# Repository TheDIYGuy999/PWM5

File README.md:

# This is an Arduino "PWM5" Solar Charge Controller

It was originally invented by Julian Ilett: https://www.youtube.com/watch?v=AobcNhLG_Xw&list=PLjzGSu1yGFjWa5BEHgX5UUrSexppett3W

This Arduino version uses a similar layout as arduined.eu: https://www.arduined.eu/arduino-solar-charge-controller/

After I designed and built a couple of own MPPT solar chargers (see my other Repositories here), I wanted to try this "classic" PWM design.
It works fine, but of course you can't use it for nominal voltages below 12V (or at least it would be very inefficient in this case). Check out the included PCB files, if you want to build your own PWM5 controller.

## Features / Improvements:
- Programmable with Arduino IDE
- Input voltage 12 - 22V (36 cell solar panel)
- Output voltage 10.8 - 14.4V (6 cell 12V lead acid battery)
- Suitable for solar palels up to 100W (according to Julian Ilett)
- Using the 3.3V, 8MHz Arduino Pro Mini, which requires about 5mA (instead of 20mA for the 5V, 16MHz version)
- IRLZ44N logic level MOSFET used, because the charge pump can't deliver enough voltage with 3.3V supply
- Working frequencies: 15kHz (charge pump), 2kHz (PWM)
- Structurized the software, added serial output, improved the LED to be similar with Julians design
- Readings and calculations are based on vcc, which is read automatically
- Much simpler differential control algorithm
- Schematic better structurized, easier to understand
- Minor component value changes
- Eagle schematic and board file available
- Gerber files available (allows you to order your own boards easily)
- This controller is COMMON NEGATIVE
- An anti backfeed diode on the solar panel side is required

New in V 1.0:
- Initial commit, tested with my 10W and 20W solar panels, charging my 12V, 6.6Ah Lead Acid Gel battery

## Usage

See pictures

Also have a look at the pdf schematic.

(c) 2018 TheDIYGuy999

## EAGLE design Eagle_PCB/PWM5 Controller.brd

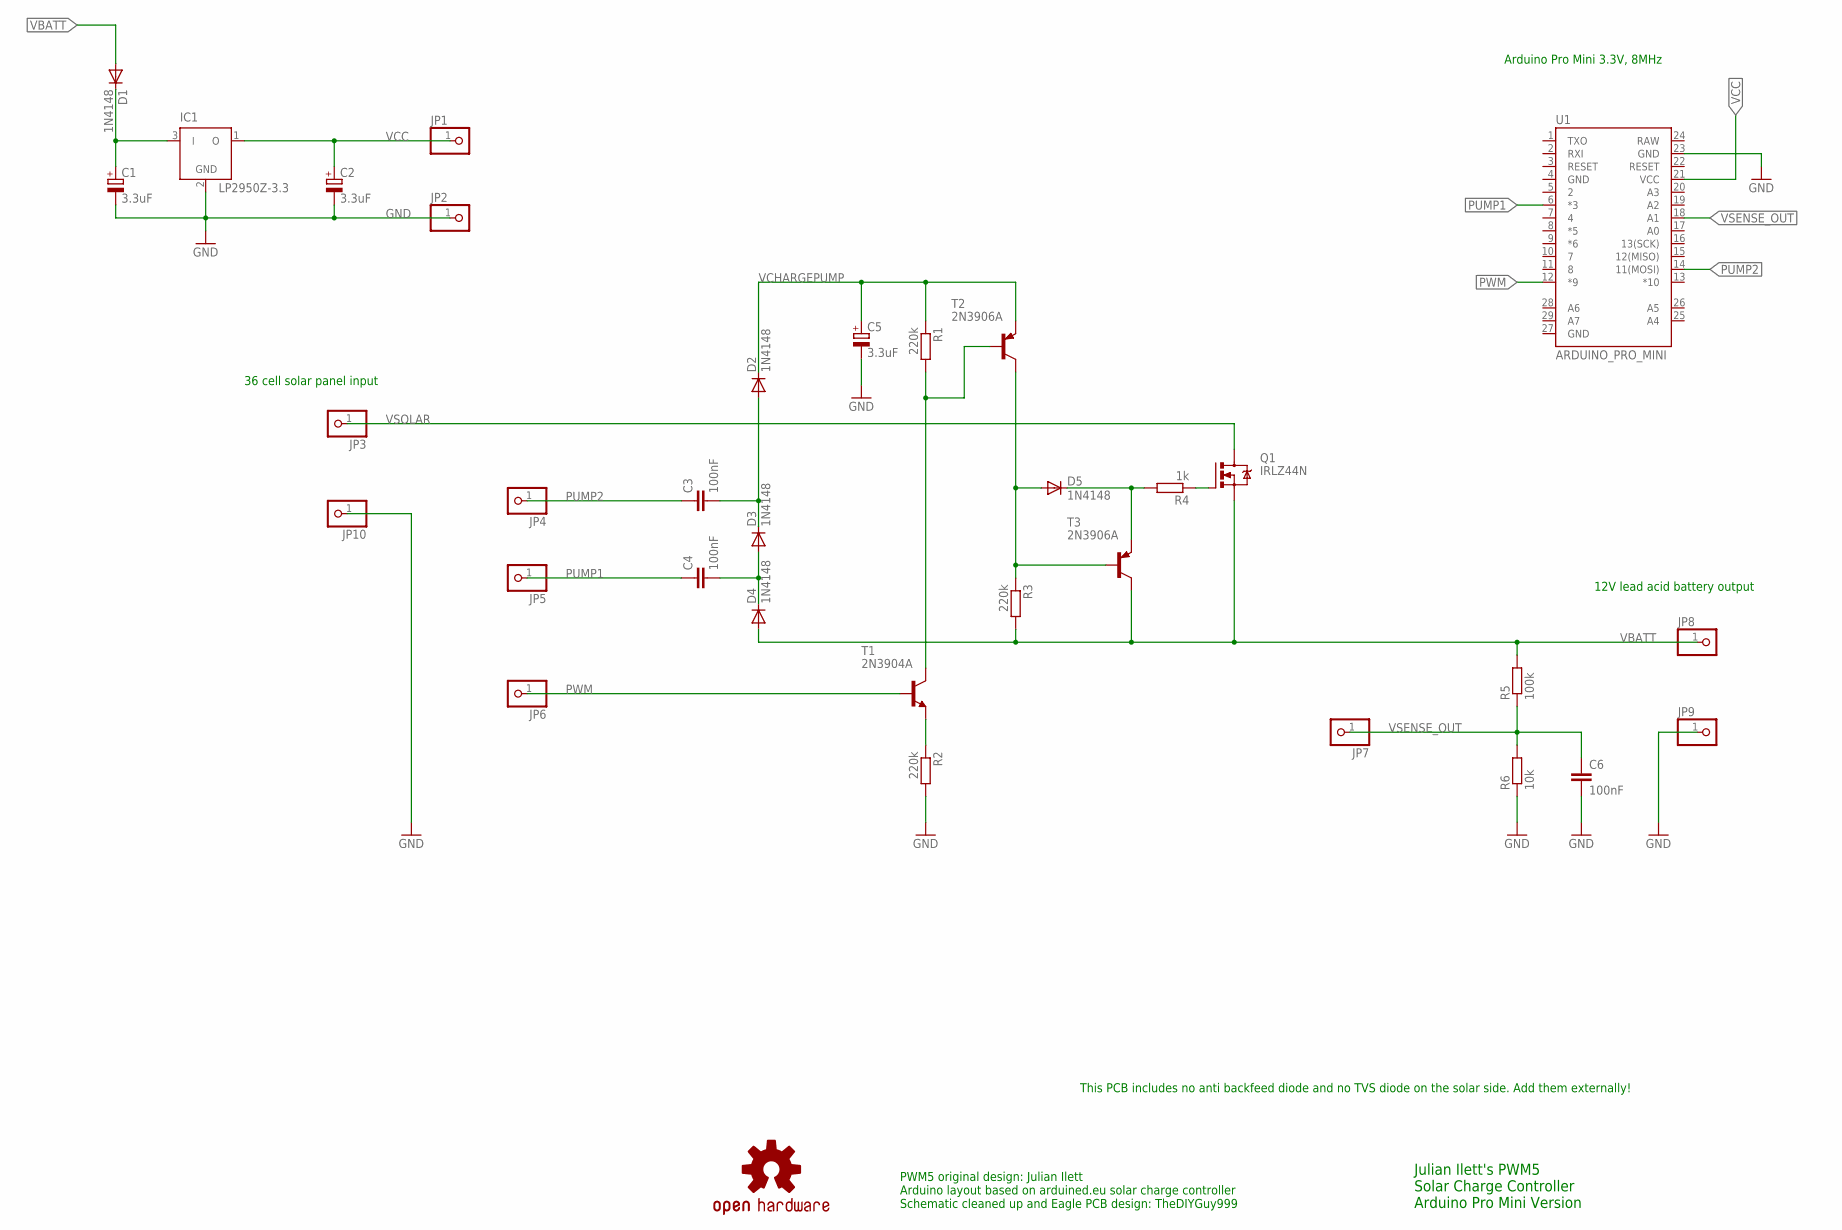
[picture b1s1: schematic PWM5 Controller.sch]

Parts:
C1, C2, C5: 3.3uF; B45181A
C3, C4: 100nF; C050-024X044
C6: 100nF; C025-024X044
D1, D4, D5: 1N4148; DO35-V
D2, D3: 1N4148; DO35-V2
IC1: LP2950Z-3.3; TO92-AMMOPACK
JP1, JP2, JP3, JP4, JP5, JP6, JP7, JP8, JP9, JP10: PINHD-1X1; 1X01
LOGO1: OSHW-LOGOS; OSHW-LOGO-S
Q1: IRLZ44N; TO220BV
R1, R2, R3: 220k; 0207/2V
R4: 1k; 0207/2V
R5: 100k; 0207/5V
R6: 10k; 0207/5V
T1: 2N3904A; TO92-AMMOPACK
T2, T3: 2N3906A; TO92-AMMOPACK
U1: ARDUINO_PRO_MINI

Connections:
GND: C1.-, C2.-, C5.-, C6.2, IC1.2 (GND), JP2.1, JP9.1, JP10.1, R2.2, R6.1, U1.23 (GND)
unnamed: D5.C, R4.2, T3.3 (E)
unnamed: Q1.G, R4.1
unnamed: C1.+, D1.C, IC1.3 (I)
unnamed: R2.1, T1.3 (E)
unnamed: D5.A, R3.1, T2.1 (C), T3.2 (B)
unnamed: R1.2, T1.1 (C), T2.2 (B)
unnamed: C4.2, D3.A, D4.C
unnamed: C3.2, D2.A, D3.C
PUMP1: C4.1, JP5.1, U1.6 (*3)
PUMP2: C3.1, JP4.1, U1.14 (11(MOSI))
PWM: JP6.1, T1.2 (B), U1.12 (*9)
VBATT: D1.A, D4.A, JP8.1, Q1.S, R3.2, R5.2, T3.1 (C)
VCC: C2.+, IC1.1 (O), JP1.1, U1.21 (VCC)
VCHARGEPUMP: C5.+, D2.C, R1.1, T2.3 (E)
VSENSE_OUT: C6.1, JP7.1, R5.1, R6.2, U1.18 (A1)
VSOLAR: JP3.1, Q1.D

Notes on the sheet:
Julian Ilett's PWM5 Solar Charge Controller Arduino Pro Mini Version
PWM5 original design: Julian Ilett Arduino layout based on arduined.eu solar charge controller Schematic cleaned up and Eagle PCB design: TheDIYGuy999
This PCB includes no anti backfeed diode and no TVS diode on the solar side. Add them externally!
Arduino Pro Mini 3.3V, 8MHz
36 cell solar panel input
12V lead acid battery output

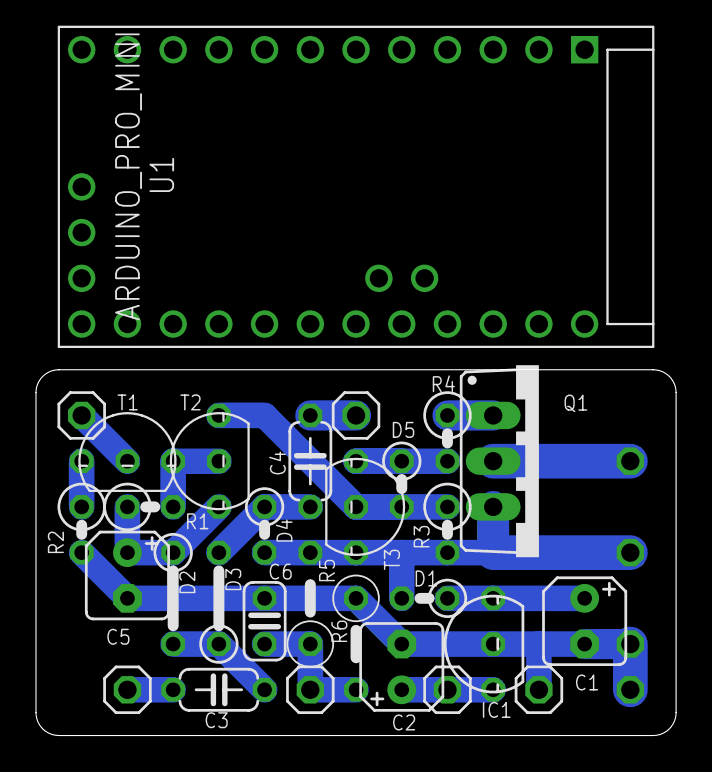
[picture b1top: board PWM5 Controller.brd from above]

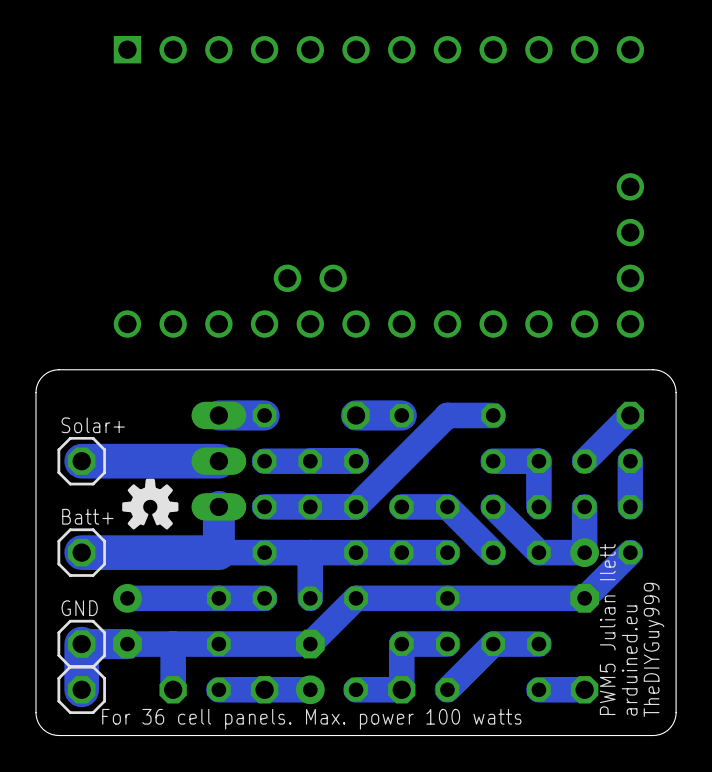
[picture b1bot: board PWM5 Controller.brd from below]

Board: 2 copper layers, 35.6 x 20.3 mm, 34 parts (5 on the bottom side), 17 nets.

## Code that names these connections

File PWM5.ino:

/* This PWM solar charge controller is based on:
    Julian Itett's PWM5: https://www.youtube.com/watch?v=AobcNhLG_Xw&list=PLjzGSu1yGFjWa5BEHgX5UUrSexppett3W
    arduined.eu's PWM solar charge controller: https://www.arduined.eu/arduino-solar-charge-controller/

    Changes and improvements, implemented by TheDIYGuy999:
    - Using the 3.3V, 8MHz Arduino Pro Mini, which requires about 5mA (instead of 20mA for the 5V, 16MHz version)
    - IRLZ44N logic level MOSFET used, because the charge pump can't deliver enough voltage with 3.3V supply
    - Structurized the software, added serial output, improved the LED to be similar with Julians design
    - Readings and calculations are based on vcc, which is read automatically
    - Much simpler differential control algorithm
    - Schematic better structurized, easier to understand
    - Minor component value changes
    - Eagle schematic and board file available
    - Gerber files available (allows you to order your own boards easily)
*/

const float codeVersion = 1.0; // Software revision

//
// =======================================================================================================
// BUILD OPTIONS (comment out unneeded options)
// =======================================================================================================
//

#define DEBUG // if not commented out, Serial.print() is active! For debugging only!!

//
// =======================================================================================================
// INCLUDE LIRBARIES
// =======================================================================================================
//

// Tabs (header files in sketch directory)
#include "readVCC.h"

// Libraries
#include <statusLED.h> // TheDIYGuy999 library: https://github.com/TheDIYGuy999/statusLED

//
// =======================================================================================================
// PIN ASSIGNMENTS & GLOBAL VARIABLES
// =======================================================================================================
//

// Pins
#define PWM 9
#define PUMP1 3
#define PUMP2 11
#define VSENSE_OUT A1

// Status LED objects
statusLED LED(false); // false = not inversed (LED wired between GND and output)

float outputVoltage;
float vcc = 3.3; // Init value only. Will be read automatically later on. Base for all our voltage readings!
float pwm; // float required for finer granularity during calculation in differential equations!

// Configuration variables (you may have to change them)
float targetOutputVoltage = 13.8; // Our maximum battery charge voltage
float voltageCalibration = 94.7; // (100k + 10k) / 10k = 11  ->  1024 / 11 = 93.09 in theory

//
// =======================================================================================================
// MAIN ARDUINO SETUP (1x during startup)
// =======================================================================================================
//

void setup() {

  // Serial port setup
#ifdef DEBUG
  Serial.begin(19200);
#endif

  // Output setup
  pinMode(PWM, OUTPUT);
  pinMode(PUMP1, OUTPUT);
  pinMode(PUMP2, OUTPUT);

  // PWM setup
  TCCR2A = TCCR2A | B00110000; // Inverting mode for charge pump
  TCCR2B = TCCR2B & B11111000 | B001; // Charge pump pins 15kHz
  TCCR1B = TCCR1B & B11111000 | B010; // PWM 1.95kHz (the maximum of this MOSFET driver circuit!)

  analogWrite(PUMP2, 117); // 117
  analogWrite(PUMP1, 137); // 137

  LED.begin(13); // Onboard LED on pin 13
}

//
// =======================================================================================================
// LED
// =======================================================================================================
//

void led() {
  if (pwm == 255) {
    // Indicate battery voltage: 13 flashes = 13V etc.
    LED.flash(20, 380, 700, outputVoltage); // ON, OFF, PAUSE, PULSES
  }

  // Indicate pwm
  else LED.flash((pwm / 2), 128 - (pwm / 2), 0, 0); // ON, OFF, PAUSE, PULSES
}

//
// =======================================================================================================
// CHECK VCC VOLTAGE
// =======================================================================================================
//

void checkVcc(boolean immediately) {

  static unsigned long lastVcc;
  if (millis() - lastVcc >= 200 || immediately) { // Every 200ms or immediately
    lastVcc = millis();
    vcc = readVcc() / 1000.0;
  }
}

//
// =======================================================================================================
// READ SENSORS
// =======================================================================================================
//

void readSensors() {
  outputVoltage = analogRead(VSENSE_OUT) * vcc / voltageCalibration;
}

//
// =======================================================================================================
// CONTROL LOOP
// =======================================================================================================
//

void controlLoop() {
  pwm += targetOutputVoltage - outputVoltage; // simple p (differential) controller
  pwm = constrain(pwm, 0, 255 );
  analogWrite(PWM, pwm);
}

//
// =======================================================================================================
// SERIAL PRINT
// =======================================================================================================
//
void serialPrint() {
#ifdef DEBUG
  static unsigned long lastPrint;
  if (millis() - lastPrint >= 1000) { // Every 1000ms
    lastPrint = millis();

    Serial.print("Setpoint: ");
    Serial.print(targetOutputVoltage);

    Serial.print(" Battery: ");
    Serial.print(outputVoltage);

    Serial.print(" PWM: ");
    Serial.print(pwm, 0);

    Serial.print(" vcc: ");
    Serial.println(vcc);
  }
#endif
}

//
// =======================================================================================================
// MAIN LOOP
// =======================================================================================================
//

void loop() {

  checkVcc(false); // with delay
  readSensors();
  controlLoop();
  led();
  serialPrint();
}

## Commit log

2018-08-12 V1.0: Initial commit
2020-11-11 Gerber file replaced

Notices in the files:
parts and their libraries:
SparkFun-Aesthetics: Licensing: Creative Commons ShareAlike 4.0 International - https://creativecommons.org/licenses/by-sa/4.0
